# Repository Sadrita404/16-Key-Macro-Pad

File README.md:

---

---

|Title | 16 Key Macro Pad|
|:-- |:--|
|Author | Sadrita Neogi|

---

## Overview
This is a macro pad that has 16 customizable switches. the keys are 4 x4 Layout . I will be mainly using it for controlling music. like play, pause, skip and replay and adding macro for opening any application

---

## Project Inspiration

### I want to make an Macro Pad  which is like this (I just draw it out of my imagination )

---
## PCB 

### For getting started I have choose Kicad for designing the PCB also the schematic 

---

---

---

---

---

## Case

### For the Case I have choose Fusion 360 for this project

---

---

---

## Top Plate 

---

### After Assembly

---

---

---

### Final Model

---

---

---

## Assembly Instructions :-

1) First we need to get the PCB and then startrd soldering the **SK6812 MINI LEDs** to all the pads of the PCB .

2) After that we need to add the **SeeedStudio XIAO** to the designated spot on the PCb .

3) Next we will solder the  **0.91 inch Blue OLED Display** to the PCB.

4) After that we will need to connect the SeeedStudio XIAO to the PC and upload the code given in the [FIRMWARE](https://github.com/Sadrita404/16-Key-Macro-Pad/blob/main/FIRMWARE/main.py) and use **Arduino IDE** to upload the code .

5) After that we will take our 3d Printed PCB Case and and screw the pcb to the case .

6) Then we will add the 3d Printed top Plate to the Case and fix it.

7) After that we will put the  Switches in the PCB gently , to all the Places.

8) And then we will add the Key Caps to the Switches.

9) The last step connect the Keyboard to the PC and start using it...

---

---

## Bill Of Material (BOM)
| Name | Purpose | Qty | Total Price (USD) | Component Link | Distributor |
|------|------|------|------|------|------|
| PCB | For adding all the component | 5 | $10.00 | [Link](https://jlcpcb.com/) | JLCPCB |
| 0.91 inch Blue OLED Display | For the Display to add in the PCB | 1 | $1.61 | [Link](https://robocraze.com/products/0-91-inch-blue-oled-display-module?variant=40194383413401&country=IN&currency=INR&utm_medium=product_sync&utm_source=google&utm_content=sag_organic&utm_campaign=sag_organic&campaignid=23607785032&adgroupid=&keyword=&device=c&gad_source=1&gad_campaignid=23597632947&gbraid=0AAAAADgHQvauLmSVauQQPRd1beTFKUXXL&gclid=Cj0KCQjw2YDQBhD_ARIsAE1qeSdtsCi1PB5ZLIsSXxdBe14DWB5-7qhPSGIfVvL-1njtE7h3b2JocGYaAlYdEALw_wcB) | Robocraze |
| M3 Heatset | For securing the PCB with the case | 4 | $0.10 | [Link](https://onlyscrews.in/products/m4-x-4mm-brass-threaded-inserts?variant=49091565650233) | Onlyscrews |
| M3x16 Bolts | For securing the PCB with the case | 16 | $0.08 | [Link](https://onlyscrews.in/products/phillips-csk-m3-x-16mm-pack-of-20?variant=48463065383225) | Onlyscrews |
| XIAO RP2040 | For Controlling the PCB | 1 | $6.35 | [Link](https://robocraze.com/products/seeed-studio-xiao-rp2040-development-board?variant=47742255562976&country=IN&currency=INR&utm_medium=product_sync&utm_source=google&utm_content=sag_organic&utm_campaign=sag_organic&campaignid=23145906364&adgroupid=182236965810&keyword=&device=c&gad_source=1&gad_campaignid=23145906364&gbraid=0AAAAADgHQvY7vNn6tBKmEbNcZWqh0FXp9&gclid=Cj0KCQjw2YDQBhD_ARIsAE1qeSdN5Bc6n-bF-js2k0JcLxiAmVTYQn5RVq83atbN41ASwhdKKu2RFEwaAmApEALw_wcB) | Robocraze |
| SK6812 MINI LEDs | For adding to the PCB (RGB) | 16 | - | [Link](https://www.desertcart.in/products/729031642-50pcs-sk6812-mini-e-rgb-similar-with-ws2812b-sk6812-3228?source=search) | Self - Source |
| Blank DSA Keycaps | For adding to the switches | 16 | $2.24 | [Link](https://meckeys.com/shop/accessories/keyboard-accessories/keycaps/blank-dsa-keycaps-1u/) | Meckeys |
| Cherry MX Switches | For the PCB where I need to place the Switch | 16 | $3.39 | [Link](https://neomacro.in/products/outemu-lemon-v3-silent?variant=50885007147286) | Neomacro |
| 1n4148 diodes | For PCB | 16 | $0.21 | [Link](https://robu.in/product/1n4148-1w-zener-diode-pack-of-50?gclid=Cj0KCQjw2YDQBhD_ARIsAE1qeSe2U2oOhGqeyOlnmYYVhdBReY2mHgCjhgFxyJprTLmK7heT-BqfC_QaAjtLEALw_wcB&gad_campaignid=17427802703&gbraid=0AAAAADvLFWcnjaEJ_u30hDzEYqbT_rE-N&gad_source=1) | Robu |
|  Total    |       |       |          |         |     $25.98  |
## For 3d Printing I have use Legion where the cost is included in the Shipping
|Tax (USD)| Shipping (USD)|
|:-- | :--|
|$14.52 |   $9|
| Total (USD)(Including BOM)   |  $49.50  |
| Round Off Total (USD)   |  $50  |

---

#### Project Under [Hack Club](https://hackclub.com/)

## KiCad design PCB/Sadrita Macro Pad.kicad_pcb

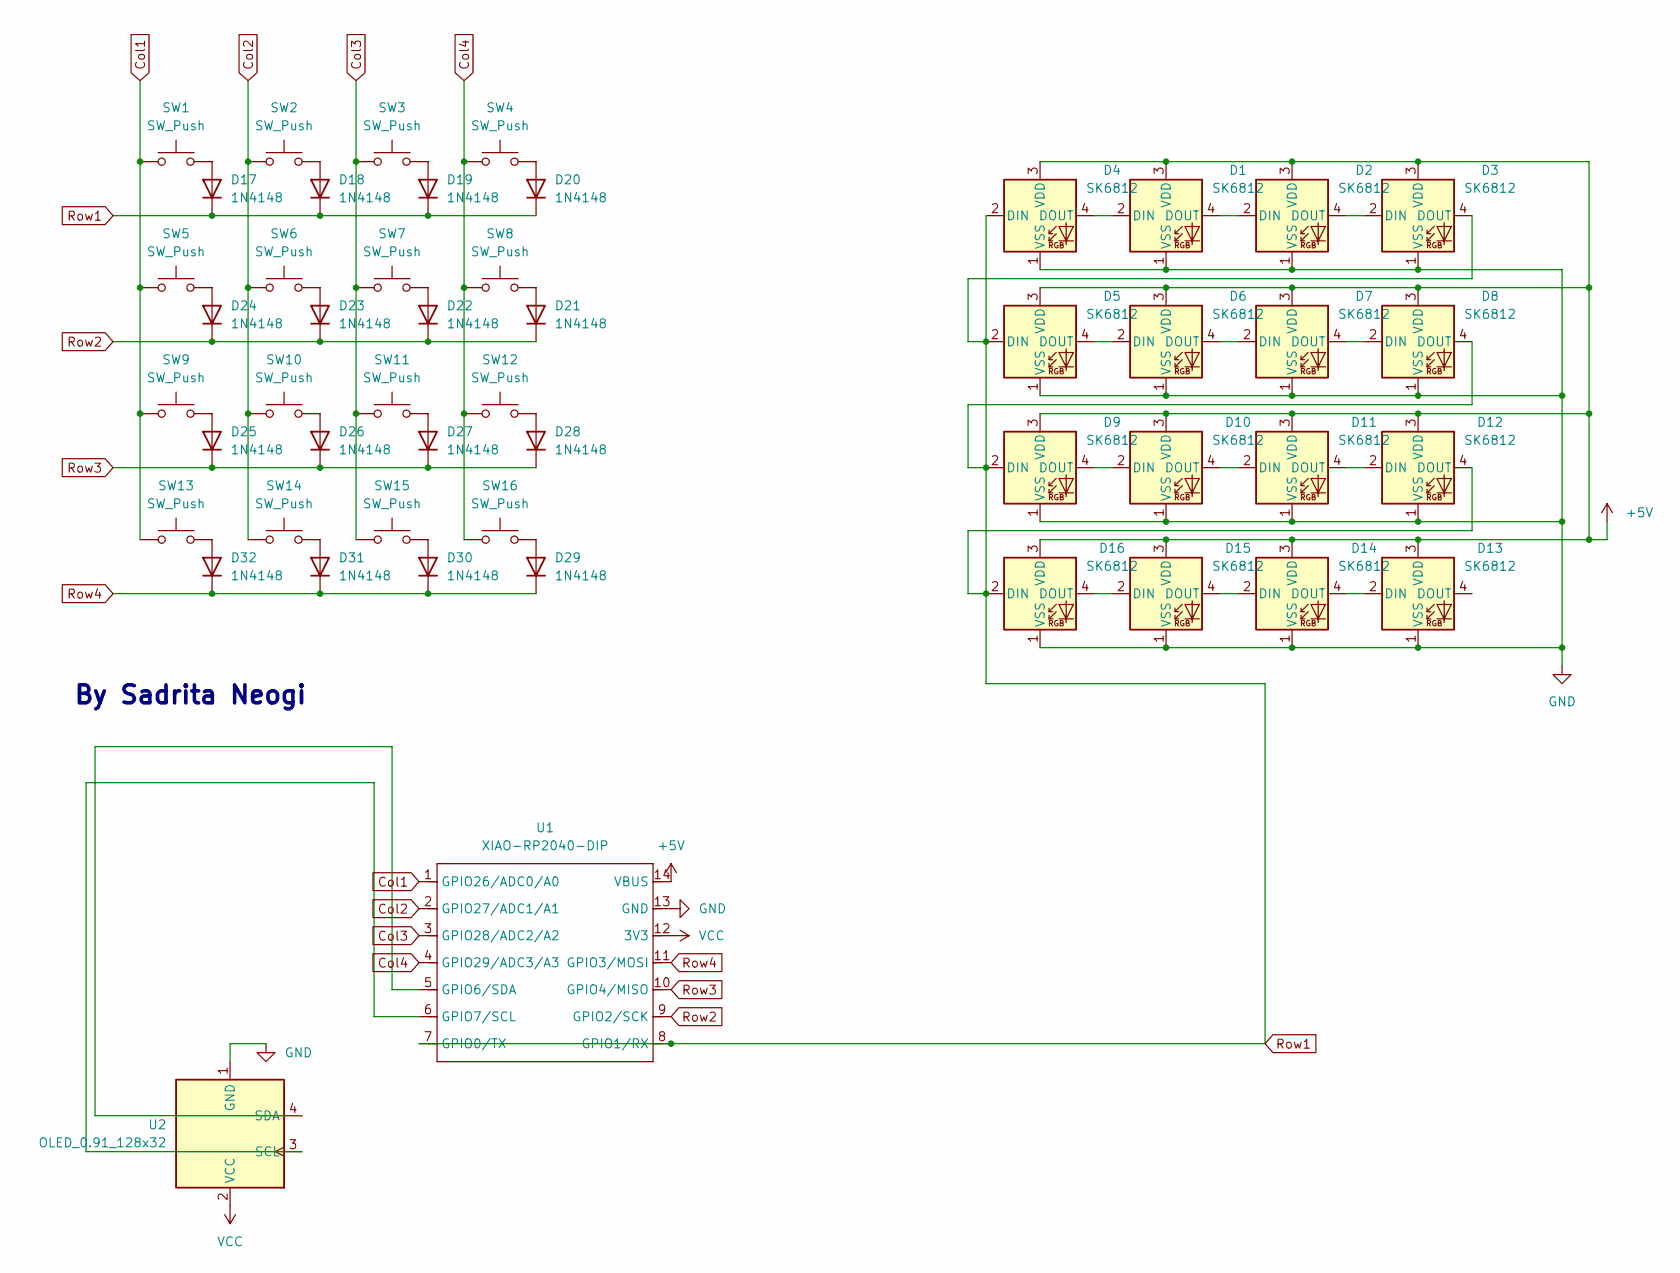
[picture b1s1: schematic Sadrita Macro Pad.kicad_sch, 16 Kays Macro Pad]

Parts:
D1, D2, D3, D4, D5, D6, D7, D8, D9, D10, D11, D12, D13, D14, D15, D16: SK6812; MX_SK6812MINI-E_REV
D17, D18, D19, D20, D21, D22, D23, D24, D25, D26, D27, D28, D29, D30, D31, D32: 1N4148; D_DO-35_SOD27_P7.62mm_Horizontal
SW1, SW2, SW3, SW4, SW5, SW6, SW7, SW8, SW9, SW10, SW11, SW12, SW13, SW14, SW15, SW16: SW_Push; SW_Cherry_MX_1.00u_PCB
U1: XIAO-RP2040-DIP
U2: OLED_0.91_128x32

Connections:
+5V: D1.3 (VDD), D2.3 (VDD), D3.3 (VDD), D4.3 (VDD), D5.3 (VDD), D6.3 (VDD), D7.3 (VDD), D8.3 (VDD), D9.3 (VDD), D10.3 (VDD), D11.3 (VDD), D12.3 (VDD), D13.3 (VDD), D14.3 (VDD), D15.3 (VDD), D16.3 (VDD), U1.14 (VBUS)
Col1: SW1.1, SW5.1, SW9.1, SW13.1, U1.1 (GPIO26/ADC0/A0)
Col2: SW2.1, SW6.1, SW10.1, SW14.1, U1.2 (GPIO27/ADC1/A1)
Col3: SW3.1, SW7.1, SW11.1, SW15.1, U1.3 (GPIO28/ADC2/A2)
Col4: SW4.1, SW8.1, SW12.1, SW16.1, U1.4 (GPIO29/ADC3/A3)
GND: D1.1 (VSS), D2.1 (VSS), D3.1 (VSS), D4.1 (VSS), D5.1 (VSS), D6.1 (VSS), D7.1 (VSS), D8.1 (VSS), D9.1 (VSS), D10.1 (VSS), D11.1 (VSS), D12.1 (VSS), D13.1 (VSS), D14.1 (VSS), D15.1 (VSS), D16.1 (VSS), U1.13 (GND), U2.1 (GND)
unnamed: D1.2 (DIN), D4.4 (DOUT)
unnamed: D1.4 (DOUT), D2.2 (DIN)
unnamed: D2.4 (DOUT), D3.2 (DIN)
unnamed: D5.4 (DOUT), D6.2 (DIN)
unnamed: D6.4 (DOUT), D7.2 (DIN)
unnamed: D7.4 (DOUT), D8.2 (DIN)
unnamed: D9.4 (DOUT), D10.2 (DIN)
unnamed: D10.4 (DOUT), D11.2 (DIN)
unnamed: D11.4 (DOUT), D12.2 (DIN)
unnamed: D13.2 (DIN), D14.4 (DOUT)
unnamed: D14.2 (DIN), D15.4 (DOUT)
unnamed: D15.2 (DIN), D16.4 (DOUT)
unnamed: D17.2 (A), SW1.2
unnamed: D18.2 (A), SW2.2
unnamed: D19.2 (A), SW3.2
unnamed: D20.2 (A), SW4.2
unnamed: D21.2 (A), SW8.2
unnamed: D22.2 (A), SW7.2
unnamed: D23.2 (A), SW6.2
unnamed: D24.2 (A), SW5.2
unnamed: D25.2 (A), SW9.2
unnamed: D26.2 (A), SW10.2
unnamed: D27.2 (A), SW11.2
unnamed: D28.2 (A), SW12.2
unnamed: D29.2 (A), SW16.2
unnamed: D30.2 (A), SW15.2
unnamed: D31.2 (A), SW14.2
unnamed: D32.2 (A), SW13.2
unnamed: U1.5 (GPIO6/SDA), U2.4 (SDA)
unnamed: U1.6 (GPIO7/SCL), U2.3 (SCL)
Row2: D21.1 (K), D22.1 (K), D23.1 (K), D24.1 (K), U1.9 (GPIO2/SCK)
Row3: D25.1 (K), D26.1 (K), D27.1 (K), D28.1 (K), U1.10 (GPIO4/MISO)
Row4: D29.1 (K), D30.1 (K), D31.1 (K), D32.1 (K), U1.11 (GPIO3/MOSI)
VCC: U1.12 (3V3), U2.2 (VCC)

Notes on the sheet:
By Sadrita Neogi

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
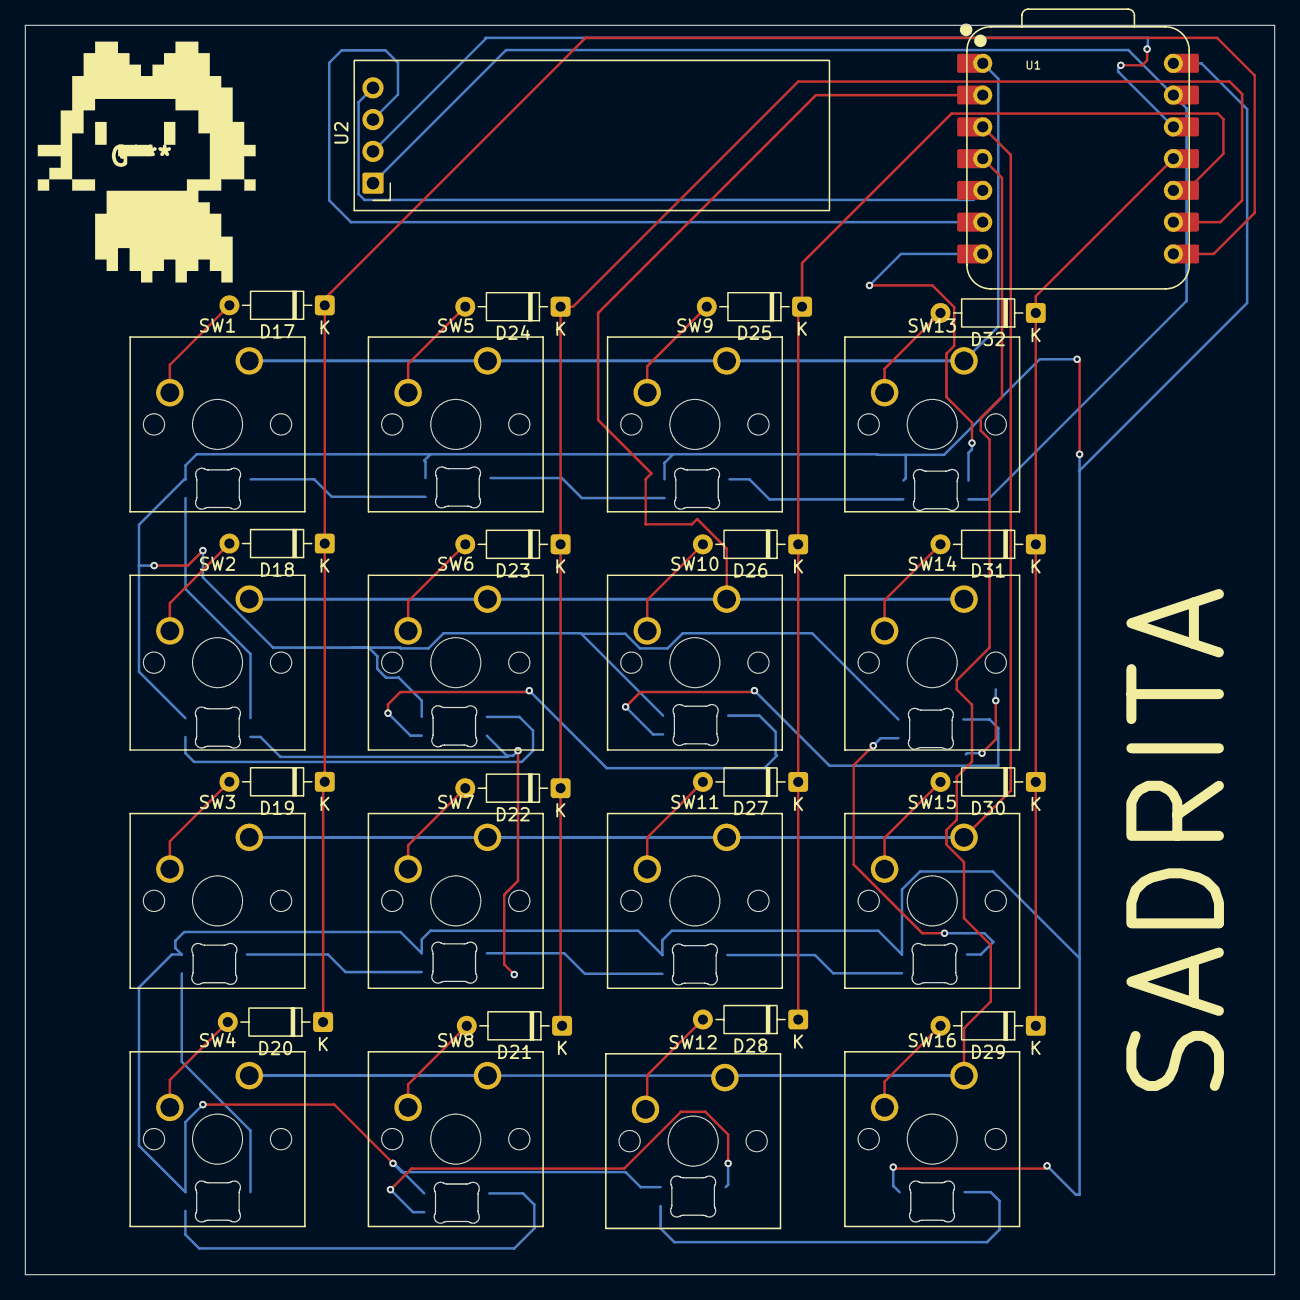
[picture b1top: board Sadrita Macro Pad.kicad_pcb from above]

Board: 2 copper layers, 99.9 x 99.9 mm, 50 parts (0 on the bottom side), 45 nets.

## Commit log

2026-05-10 BOM added
2026-05-10 Bill added
2026-05-10 BOM added of the project ( csv )
2026-05-25 Create LICENSE
